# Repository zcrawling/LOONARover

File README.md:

# LOONAR

로버: Raspberry Pi 5 · Control/Payload Teensy 4.1 · RoboClaw.
지상국 명령은 cFS와 vehicle_gatewayd를 거쳐 Control MCU로 전달한다.

## 실행

준비된 Pi에서:

```bash
bash ~/LOONAR/platforms/loonar/tools/start-ground-support.sh --video
```

`--video`는 SSH 접속 PC로 영상을 보낸다. SSH 밖에서는 `--video-ip 지상국IP`를 사용한다.
지상국 PC에서:

```bash
cd ~/LOONAR
bash GCS/scripts/start_loonar_gcs.sh 192.168.0.14
```

주소는 실제 Pi IP로 바꾼다. 웹 화면은 `http://127.0.0.1:8080`이다.

- [Pi 준비·실행·기록](platforms/loonar/porting/ground_control_runbook.md)
- [지상국 사용법](GCS/README.md)
- [Control 펌웨어 빌드·업로드와 배선](platforms/loonar/firmware/control/README.md)
- [Payload 측정](platforms/loonar/porting/payload_pca_runbook.md)
- [구조와 명령 경로](docs/architecture.md) · [문서 목록](docs/README.md)

## 저장소

| 경로 | 내용 |
| --- | --- |
| `GCS/` | 웹 UI, 키보드·Xbox 입력, 영상 수신 |
| `cfs/` | GroundLink, 차량·MCU·Payload 앱 |
| `common/` | Gateway, 통신 codec, 공통 ROS·영상 도구 |
| `platforms/loonar/` | Pi 배포, MCU 펌웨어, 하드웨어·PCB |
| `platforms/limo/` | LIMO 시험 플랫폼과 검증 기록 |
| `tools/` | 통합 시험, 영상·센서·주행 분석 도구 |
| `data/`, `output/` | 실험 원본과 결과 |

문서는 저장소 소스 기준이다. Pi 설치본과 MCU에 업로드된 이미지가 같다는 뜻은 아니다.
날짜가 붙은 측정·제작 기록은 당시 결과로 읽는다.

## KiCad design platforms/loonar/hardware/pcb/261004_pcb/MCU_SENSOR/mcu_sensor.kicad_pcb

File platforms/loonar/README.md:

# LOONAR 로버

Raspberry Pi 5 / Ubuntu 24.04 / ROS 2 Jazzy와 두 Teensy 4.1을 사용한다.
Control은 FreeRTOS·LNR2 USB, Payload는 별도 센서 펌웨어·USB ASCII 경로다.

- [실행·로그·기록](porting/ground_control_runbook.md)
- [Pi 설치](deploy/README.md)
- [배선](hardware/hardware_baseline.md) · [CAD 기반 TF](ros2/loonar_description/README.md)
- [Control 펌웨어](firmware/control/README.md) · [wire v2](porting/mcu_wire_v2.md)
- [Payload 펌웨어](firmware/payload/README.md) · [운용](porting/payload_pca_runbook.md)
- [CubeEye 공급 SDK](vendor-assets.md) · [ToF 기록](porting/tof_recording_runbook.md)

`interfaces/control_mcu_wire_v1.md`와 C 기반 control core는 이전 프로토콜의
회귀시험 자료다. 현재 `src/v2/runtime.cpp`와 혼동하지 않는다.

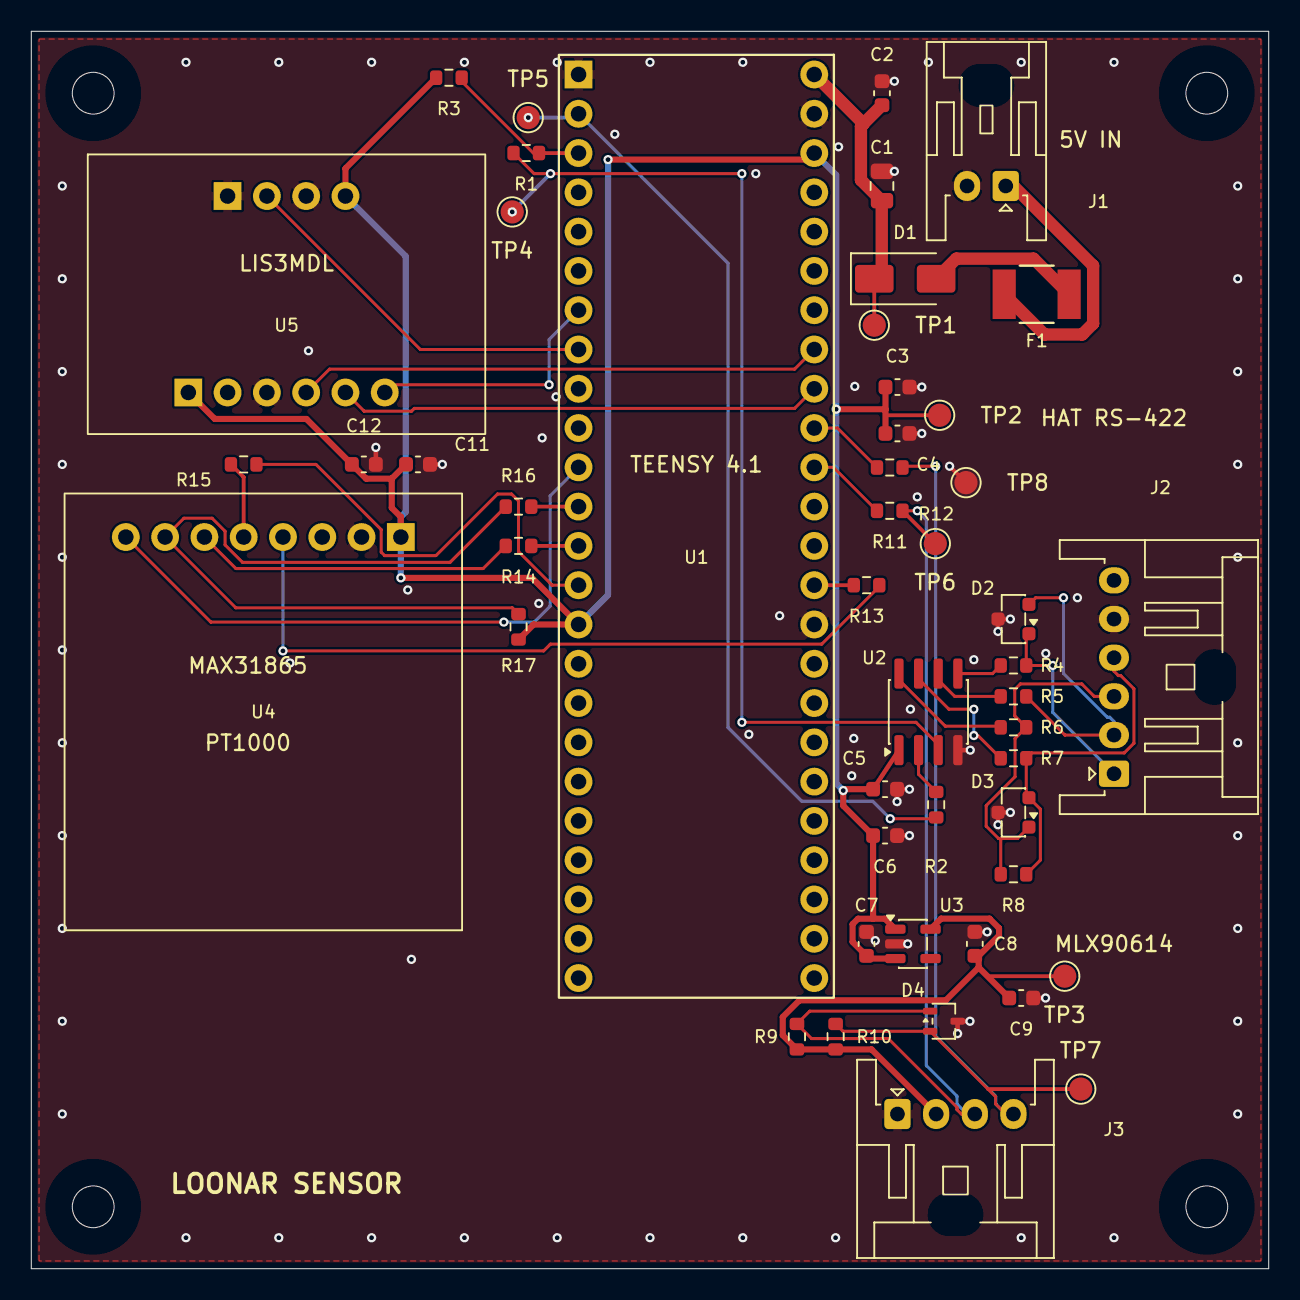
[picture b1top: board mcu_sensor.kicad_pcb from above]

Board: 4 copper layers, 80.0 x 80.0 mm, 53 parts (0 on the bottom side), 35 nets.

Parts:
C1: 10uF / 50V / X5R; C_0805_2012Metric
C2, C4, C5, C9, C11: 100nF / 50V / X7R; C_0603_1608Metric
C3: 4.7uF / 16V / X5R; C_0603_1608Metric
C6, C7, C12: 1uF / 25V / X7R; C_0603_1608Metric
C8: 2.2uF / 10V / X7R; C_0603_1608Metric
D1: B340A-13-F / 40V 3A; D_SMA
D2, D3: CDSOT23-SM712; Bourns_CDSOT23_SM712
D4: TPD2E2U06QDCKRQ1; SOT-323_SC-70
F1: PTC / 0.5A hold / 15V; PTC_Bourns_MF_MSMF050_1812
H1, H2, H3, H4: M2.5 / NPTH 2.7mm; MountingHole_2.7mm_M2.5
J1: 5V IN / XA 2P; JST_XA_S02B-XASK-1_1x02_P2.50mm_Horizontal
J2: HAT RS422 / XA 6P; JST_XA_S06B-XASK-1_1x06_P2.50mm_Horizontal
J3: MLX90614 / XA 4P; JST_XA_S04B-XASK-1_1x04_P2.50mm_Horizontal
R1, R2, R11, R12: 47R; R_0603_1608Metric
R3, R17: 10k; R_0603_1608Metric
R4, R5, R6, R7: 10R / 1% / HP pulse; R_0603_1608Metric
R8: 120R; R_0603_1608Metric
R9, R10: 2.2k; R_0603_1608Metric
R13, R14, R15, R16: 33R / 1%; R_0603_1608Metric
TP1: 5V; TestPoint_Pad_D1.5mm
TP2: 3V3; TestPoint_Pad_D1.5mm
TP3: IR3V; TestPoint_Pad_D1.5mm
TP4: TX; TestPoint_Pad_D1.5mm
TP5: RX; TestPoint_Pad_D1.5mm
TP6: SCL; TestPoint_Pad_D1.5mm
TP7: SDA; TestPoint_Pad_D1.5mm
TP8: GND; TestPoint_Pad_D1.5mm
U1: Teensy 4.1; Teensy41_48Pin
U2: THVD1451DR; SOIC-8_3.9x4.9mm_P1.27mm
U3: TLV75730PDBVR / 3.0V; SOT-23-5
U4: MAX31865 / Rref 4.3k; Adafruit_MAX31865_Carrier
U5: LIS3MDL / Adafruit 4479; Adafruit_LIS3MDL_Carrier

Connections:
+3V0_IR: C8.1, C9.1, J3.2, R9.1, R10.1, TP3.1, U3.5 (OUT)
+3V3: C3.1, C4.1, C5.1, C6.1, C7.1, C11.1, C12.1, R3.1, R17.1, TP2.1, U1.3.3V_1 (3.3V), U1.3.3V_2 (3.3V), U2.1 (VCC), U3.1 (IN), U3.3 (EN), U4.JP1_1 (VIN_3.3V), U5.JP1_4 (CS_-_I2C_HIGH), U5.JP4_1 (VIN_3.3V)
+5V_IN: F1.1, J1.1
+5V_MAIN: C1.1, C2.1, D1.1 (K), TP1.1, U1.VIN (VIN_5V)
FUSED_5V: D1.2 (A), F1.2
GND: C1.2, C2.2, C3.2, C4.2, C5.2, C6.2, C7.2, C8.2, C9.2, C11.2, C12.2, D2.3 (GND), D3.3 (GND), D4.3, J1.2, J2.5, J3.1, TP8.1, U1.GND1 (GND), U1.GND2 (GND), U1.GND3 (GND), U2.4 (GND), U3.2 (GND), U4.JP1_2 (GND), U5.JP1_1 (GND), U5.JP1_3 (DO_/_ADDR), U5.JP4_3 (GND)
IR_SCL: D4.1, J3.3, R9.2, R11.2, TP6.1
IR_SCL_MCU: R11.1, U1.16 (A2)
IR_SDA: D4.2, J3.4, R10.2, R12.2, TP7.1
IR_SDA_MCU: R12.1, U1.17 (A3)
LINK_RX_N: D3.2 (LINE2), J2.4, R7.2, R8.2
LINK_RX_P: D3.1 (LINE1), J2.3, R6.2, R8.1
LINK_TX_N: D2.2 (LINE2), J2.2, R5.2
LINK_TX_P: D2.1 (LINE1), J2.1, R4.2
MAG_DRDY: U1.6 (OUT1D), U5.JP1_2 (DRDY)
MAG_INT: U1.5 (IN2), U5.JP4_6 (INT)
MAG_SCL: U1.19 (A5), U5.JP4_4 (SCL)
MAG_SDA: U1.18 (A4), U5.JP4_5 (SDA)
RS_A: R6.1, U2.8 (A)
RS_B: R7.1, U2.7 (B)
RS_DI: R1.2, TP4.1, U2.3 (D)
RS_RO: R2.1, U2.2 (R)
RS_Y: R4.1, U2.5 (Y)
RS_Z: R5.1, U2.6 (Z)
RTD_CS: R16.2, R17.2, U4.JP1_7 (CS)
RTD_CS_MCU: R16.1, U1.10 (CS1)
RTD_MISO: R15.1, U4.JP1_5 (SDO_/_MISO)
RTD_MOSI: R14.2, U4.JP1_6 (SDI_/_MOSI)
RTD_RDY: U1.9 (OUT1C), U4.JP1_8 (RDY)
RTD_SCK: R13.2, U4.JP1_4 (CLK)
SPI_MISO_MCU: R15.2, U1.12 (MISO)
SPI_MOSI_MCU: R14.1, U1.11 (MOSI)
SPI_SCK_MCU: R13.1, U1.13 (SCK)
UART1_RX: R2.2, TP5.1, U1.0 (RX1)
UART1_TX: R1.1, R3.2, U1.1 (TX1)

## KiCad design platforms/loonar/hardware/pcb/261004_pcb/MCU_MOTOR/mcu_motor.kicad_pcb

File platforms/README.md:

# Vehicle Platforms

Platform folders contain only hardware, firmware, launch/configuration and HIL
assets that genuinely differ between vehicles. Shared mission, ROS autonomy and
Gateway logic belongs in common modules.

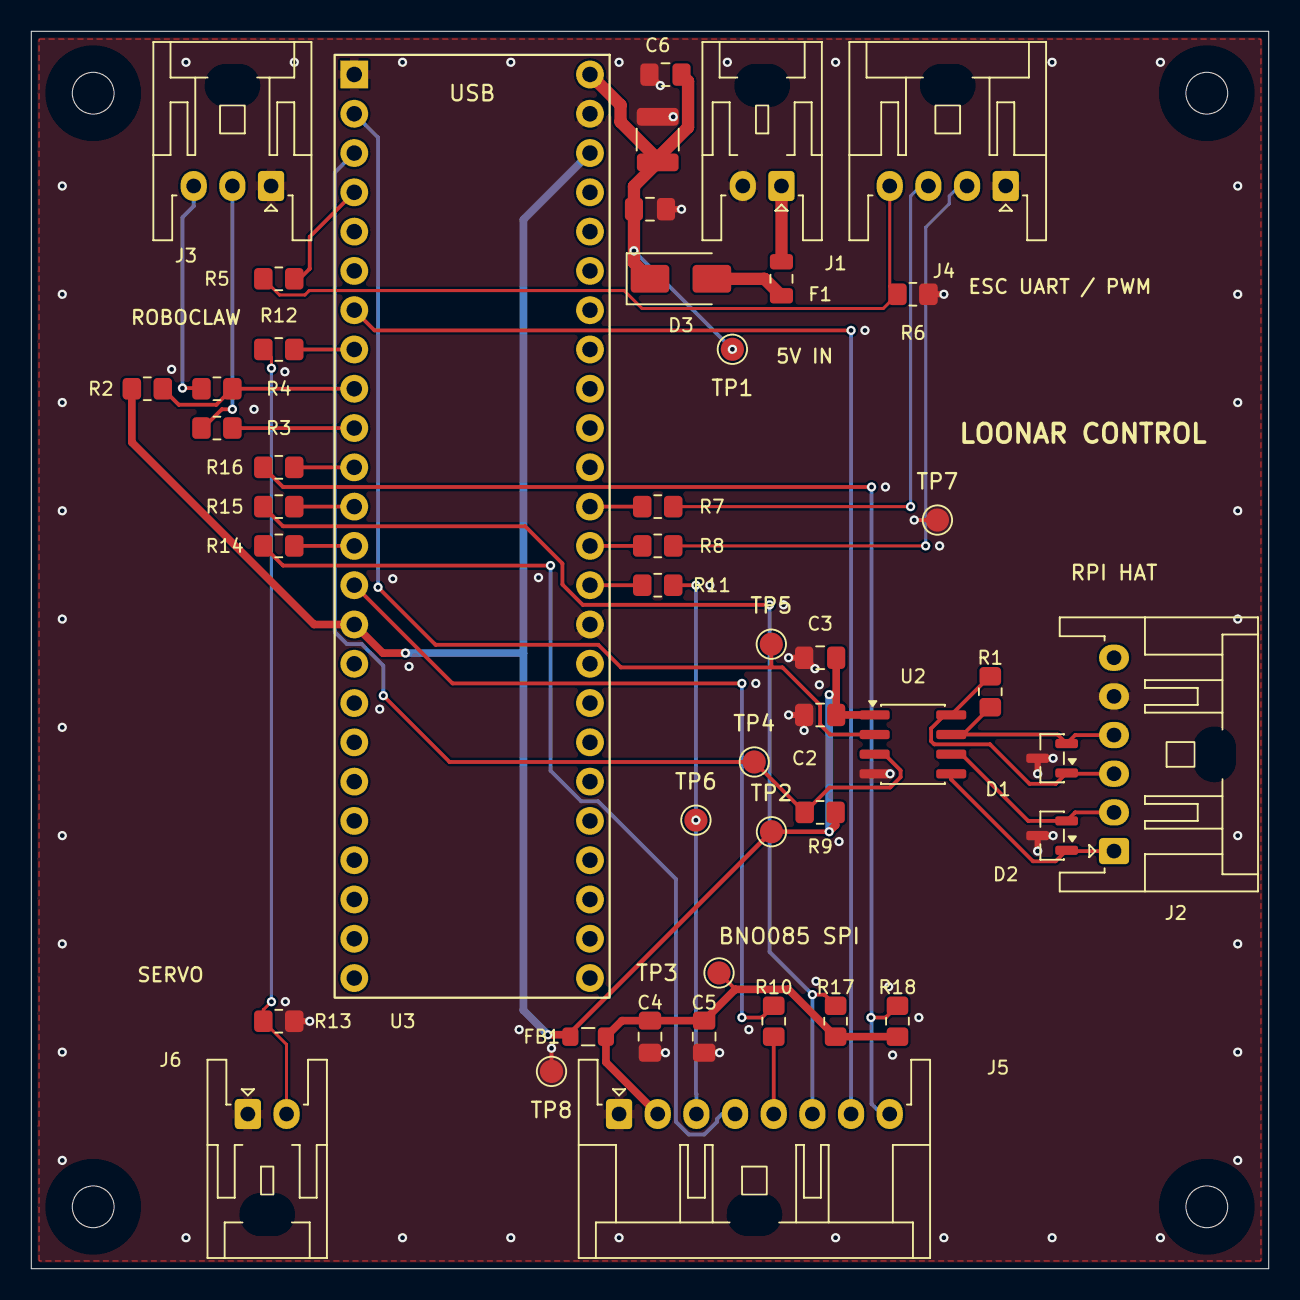
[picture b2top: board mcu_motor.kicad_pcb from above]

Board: 4 copper layers, 80.0 x 80.0 mm, 50 parts (0 on the bottom side), 35 nets.

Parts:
C2, C4, C6: 100nF / 50V / X7R; C_0805_2012Metric_Pad1.18x1.45mm_HandSolder
C3, C8: 1uF / 50V / X7R; C_0805_2012Metric_Pad1.18x1.45mm_HandSolder
C5: 4.7uF / 25V / X5R; C_0805_2012Metric_Pad1.18x1.45mm_HandSolder
C7: 47uF / 16V / X5R; C_1210_3225Metric
D1, D2: SM712-02HTG; SOT-23
D3: B340A-13-F / 40V 3A; D_SMA
F1: PTC / 0.75A hold / 6V; Fuse_MF_PSMF_0805
FB1: 220R@100MHz / 2A; L_0805_2012Metric_Pad1.05x1.20mm_HandSolder
H1, H2, H3, H4: M2.5 / NPTH 2.7mm; MountingHole_2.7mm_M2.5
J1: 5V IN / XA 2P; JST_XA_S02B-XASK-1_1x02_P2.50mm_Horizontal
J2: HAT RS422 / XA 6P; JST_XA_S06B-XASK-1_1x06_P2.50mm_Horizontal
J3: RoboClaw UART / XA 3P; JST_XA_S03B-XASK-1_1x03_P2.50mm_Horizontal
J4: ESC UART PWM / XA 4P; JST_XA_S04B-XASK-1_1x04_P2.50mm_Horizontal
J5: BNO085 SPI / XA 8P; JST_XA_S08B-XASK-1_1x08_P2.50mm_Horizontal
J6: TR5 PWM / XA 2P; JST_XA_S02B-XASK-1_1x02_P2.50mm_Horizontal
R1: 120R / 1%; R_0805_2012Metric_Pad1.20x1.40mm_HandSolder
R2: 4.7k / 1%; R_0805_2012Metric_Pad1.20x1.40mm_HandSolder
R3, R4, R5, R7, R8, R12, R16: 100R / 1%; R_0805_2012Metric_Pad1.20x1.40mm_HandSolder
R6, R9, R13, R17, R18: 10k / 1%; R_0805_2012Metric_Pad1.20x1.40mm_HandSolder
R10, R11, R14, R15: 33R / 1%; R_0805_2012Metric_Pad1.20x1.40mm_HandSolder
TP1: 5V; TestPoint_Pad_D1.5mm
TP2: 3V3; TestPoint_Pad_D1.5mm
TP3: IMU3V; TestPoint_Pad_D1.5mm
TP4: TX; TestPoint_Pad_D1.5mm
TP5: RX; TestPoint_Pad_D1.5mm
TP6: SCK; TestPoint_Pad_D1.5mm
TP7, TP8: GND; TestPoint_Pad_D1.5mm
U2: THVD1451DR; SOIC-8_3.9x4.9mm_P1.27mm
U3: Teensy 4.1; Teensy41_48Pin

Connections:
5V_IN: F1.1, J1.1
+3V3: C2.1, C3.1, FB1.1, R2.1, R9.2, TP2.1, U2.1 (VCC), U3.3.3V_1 (3.3V), U3.3.3V_2 (3.3V)
+3V3_IMU: C4.2, C5.2, FB1.2, J5.2, R17.1, R18.1, TP3.1
+5V_MAIN: C6.1, C7.1, C8.1, D3.1 (K), TP1.1, U3.VIN (VIN_5V)
B-G431B RX: J4.2, R8.1
B-G431B TX: J4.3, R7.1
B_G431B PWM: J4.4, R5.1, R6.1
GND: C2.2, C3.2, C4.1, C5.1, C6.2, C7.2, C8.2, D1.3 (common), D2.3 (common), J1.2, J2.5, J3.1, J4.1, J5.1, J6.1, R6.2, R13.2, TP7.1, TP8.1, U2.4 (GND), U3.GND1 (GND), U3.GND2 (GND), U3.GND3 (GND)
IMU_CS: J5.6, R15.1, R17.2
IMU_CS_MCU: R15.2, U3.10 (CS1)
IMU_INT: J5.7, U3.5 (IN2)
IMU_MISO: J5.5, R10.1
IMU_MISO_MCU: R10.2, U3.12 (MISO)
IMU_MOSI: J5.4, R14.1
IMU_MOSI_MCU: R14.2, U3.11 (MOSI)
IMU_RST: J5.8, R16.1, R18.2
IMU_RST_MCU: R16.2, U3.9 (OUT1C)
IMU_SCK: J5.3, R11.1, TP6.1
IMU_SCK_MCU: R11.2, U3.13 (SCK)
unnamed: D3.2 (A), F1.2
RS485_RX+: D1.1 (A1), J2.3, R1.1, U2.8 (A)
RS485_RX-: D1.2 (A2), J2.4, R1.2, U2.7 (B)
RS485_TX+: D2.1 (A1), J2.1, U2.5 (Y)
RS485_TX-: D2.2 (A2), J2.2, U2.6 (Z)
RoboClaw RX: J3.2, R3.1
RoboClaw TX: J3.3, R4.1
SERVO_PWM: J6.2, R12.1, R13.1
SERVO_PWM_MCU: R12.2, U3.6 (OUT1D)
Teensy_Pin2: R5.2, U3.2 (OUT2)
Teensy_RX1: TP5.1, U2.2 (R), U3.0 (RX1)
Teensy_RX2: R2.2, R4.2, U3.7 (RX2)
Teensy_RX3: R7.2, U3.15 (A1)
Teensy_TX1: R9.1, TP4.1, U2.3 (D), U3.1 (TX1)
Teensy_TX2: R3.2, U3.8 (TX2)
Teensy_TX3: R8.2, U3.14 (A0)

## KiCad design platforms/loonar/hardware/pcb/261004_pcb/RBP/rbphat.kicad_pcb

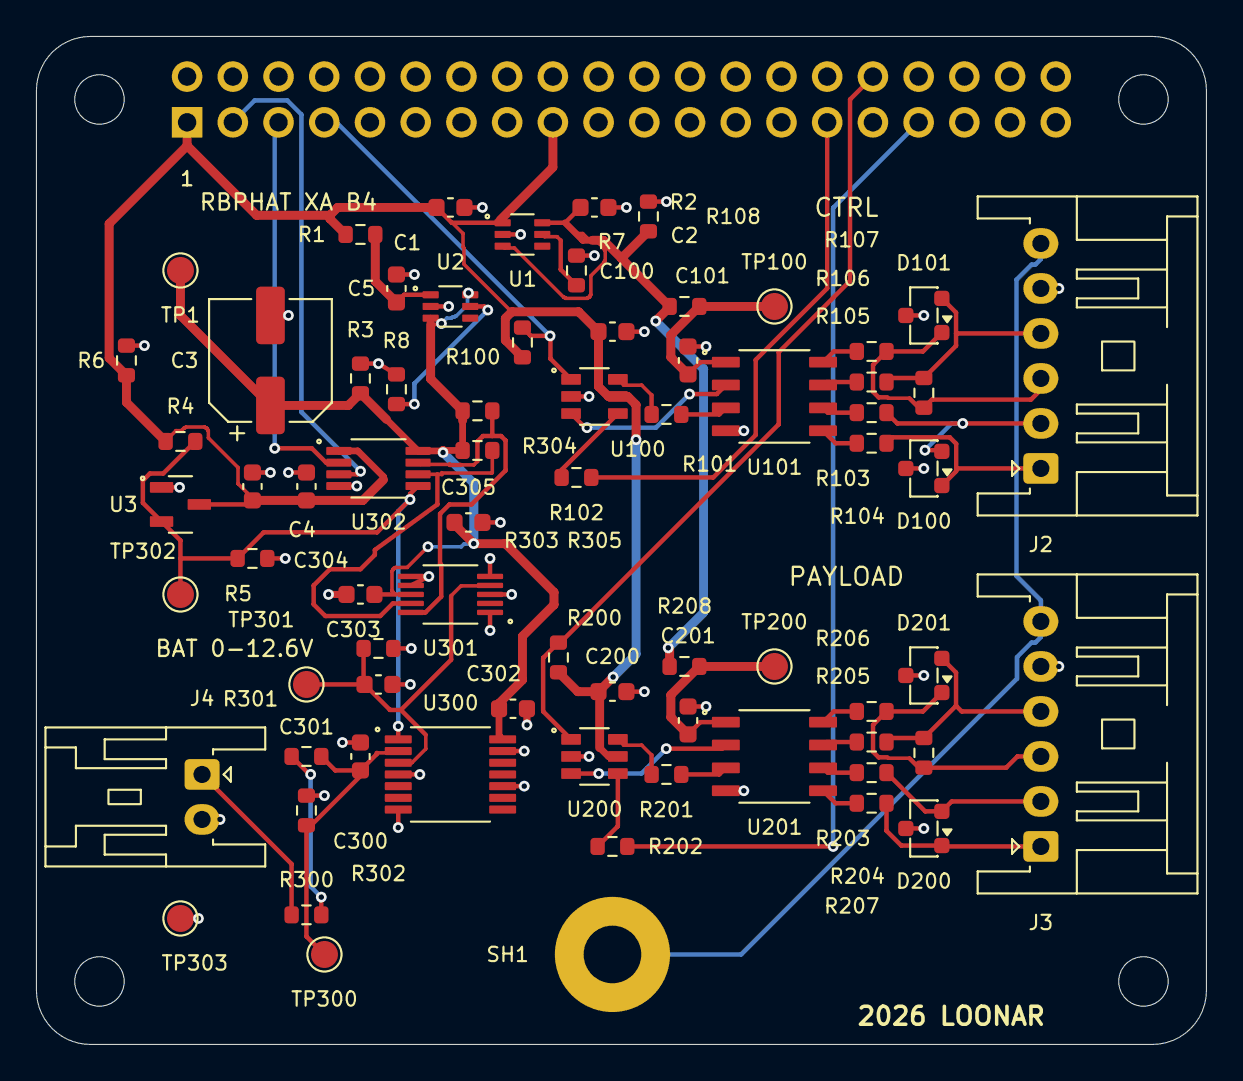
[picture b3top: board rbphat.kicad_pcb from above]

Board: 4 copper layers, 65.0 x 56.0 mm, 77 parts (1 on the bottom side), 47 nets.

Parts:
C1, C5, C300: 1uF / 25V / X7R; Capacitor_SMD_C_0603_1608Metric
C2: 4.7uF / 16V / X5R; Capacitor_SMD_C_0603_1608Metric
C3: 100uF / 16V / polarized; Panasonic_FK_D_6.3x5.8
C4, C100, C101, C200, C201, C302, C303, C304, C305: 100nF / 50V / X7R; Capacitor_SMD_C_0603_1608Metric
C301: 1nF / 50V / C0G; Capacitor_SMD_C_0603_1608Metric
D100, D101, D200, D201: CDSOT23-SM712; Bourns_CDSOT23_SM712
H1, H2, H3, H4: M2.5 / NPTH 2.75mm
J1: Raspberry Pi GPIO / 2x20; GPIO_2x20_H16_Drill1.02
J2: CTRL RS422 / XA 6P; XA_S06B_Horizontal
J3: PAYLOAD RS422 / XA 6P; XA_S06B_Horizontal
J4: BAT 0-12.6V / XA 2P; XA_S02B_Horizontal
R1: 22R / 1% / HP pulse; Resistor_SMD_R_0603_1608Metric
R2, R3, R4, R7, R8, R100, R200: 10k; Resistor_SMD_R_0603_1608Metric
R5: 100k; Resistor_SMD_R_0603_1608Metric
R6: 1k; Resistor_SMD_R_0603_1608Metric
R101, R102, R201, R202: 47R; Resistor_SMD_R_0603_1608Metric
R103, R104, R105, R106, R203, R204, R205, R206: 10R / 1% / HP pulse; Resistor_SMD_R_0603_1608Metric
R107, R207: 120R; Resistor_SMD_R_0603_1608Metric
R108, R208: 0R; Resistor_SMD_R_0603_1608Metric
R300, R301, R303: 47k / 0.1%; Resistor_SMD_R_0603_1608Metric
R302: 18k / 0.1%; Resistor_SMD_R_0603_1608Metric
R304, R305: 4.7k; Resistor_SMD_R_0603_1608Metric
SH1: CHASSIS / M3 ring terminal; Chassis_M3_Plated
TP1: ANA supply; TestPoint_TestPoint_Pad_D1.5mm
TP100: CTRL_VCC; TestPoint_TestPoint_Pad_D1.5mm
TP200: PAY_VCC; TestPoint_TestPoint_Pad_D1.5mm
TP300: BAT_DIV; TestPoint_TestPoint_Pad_D1.5mm
TP301: BAT_ADC; TestPoint_TestPoint_Pad_D1.5mm
TP302: POWER_GOOD; TestPoint_TestPoint_Pad_D1.5mm
TP303: GND; TestPoint_TestPoint_Pad_D1.5mm
U1, U2: LM66100DCKR; TI_DCK0006A
U3: TLV803ED29DBZR; TI_DBZ0003A
U100, U200: SN74LVC2G17DBVT; TI_DBV0006A
U101, U201: THVD1451DR; TI_D0008A
U300: TMUX1511PWR; TI_PW0014A
U301: ADS1115IDGSR; TI_DGS0010A
U302: TCA9517ADGKR; TI_DGK0008A

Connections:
+3V3_ANA: C3.1, C302.1, C303.1, C305.1, R3.1, R304.1, R305.1, TP1.1, U2.3, U2.6, U300.14, U301.8, U302.8
+3V3_PI: C1.1, C4.1, C100.1, C200.1, C304.1, J1.1, J1.17, R1.1, R4.1, R6.1, R100.1, R200.1, U1.1, U3.3, U100.5, U200.5, U302.1
+3V3_RS: C2.1, R2.1, R108.1, R208.1, U1.3, U1.6
/ANA_FEED: C5.1, R1.2, U2.1
/ANA_STATUS_UNUSED: R8.1, U2.5
/Battery sensing and I2C isolation/ADC_SCL: R304.2, U301.10, U302.7
/Battery sensing and I2C isolation/ADC_SDA: R305.2, U301.9, U302.6
/Battery sensing and I2C isolation/BAT_ADC: C301.1, R303.1, TP301.1, U300.3, U301.4
/Battery sensing and I2C isolation/BAT_DIV: C300.1, R301.2, R302.1, TP300.1, U300.2
/Battery sensing and I2C isolation/BAT_MID: R300.2, R301.1
/Battery sensing and I2C isolation/BAT_RAW: J4.1, R300.1
/CTRL full-duplex RS-422/CTRL_A: R105.1, U101.8
/CTRL full-duplex RS-422/CTRL_B: R106.1, U101.7
/CTRL full-duplex RS-422/CTRL_DI: R101.2, U101.3
/CTRL full-duplex RS-422/CTRL_RO: U100.3, U101.2
/CTRL full-duplex RS-422/CTRL_RX+: D101.1, J2.3, R105.2, R107.1
/CTRL full-duplex RS-422/CTRL_RX-: D101.2, J2.4, R106.2, R107.2
/CTRL full-duplex RS-422/CTRL_RX_BUF: R102.1, U100.4
/CTRL full-duplex RS-422/CTRL_TX+: D100.1, J2.1, R103.2
/CTRL full-duplex RS-422/CTRL_TX-: D100.2, J2.2, R104.2
/CTRL full-duplex RS-422/CTRL_TX_BUF: R101.1, U100.6
/CTRL full-duplex RS-422/CTRL_VCC: C101.1, R108.2, TP100.1, U101.1
/CTRL full-duplex RS-422/CTRL_Y: R103.1, U101.5
/CTRL full-duplex RS-422/CTRL_Z: R104.1, U101.6
/PAY full-duplex RS-422/PAY_A: R205.1, U201.8
/PAY full-duplex RS-422/PAY_B: R206.1, U201.7
/PAY full-duplex RS-422/PAY_DI: R201.2, U201.3
/PAY full-duplex RS-422/PAY_RO: U200.3, U201.2
/PAY full-duplex RS-422/PAY_RX+: D201.1, J3.3, R205.2, R207.1
/PAY full-duplex RS-422/PAY_RX-: D201.2, J3.4, R206.2, R207.2
/PAY full-duplex RS-422/PAY_RX_BUF: R202.1, U200.4
/PAY full-duplex RS-422/PAY_TX+: D200.1, J3.1, R203.2
/PAY full-duplex RS-422/PAY_TX-: D200.2, J3.2, R204.2
/PAY full-duplex RS-422/PAY_TX_BUF: R201.1, U200.6
/PAY full-duplex RS-422/PAY_VCC: C201.1, R208.2, TP200.1, U201.1
/PAY full-duplex RS-422/PAY_Y: R203.1, U201.5
/PAY full-duplex RS-422/PAY_Z: R204.1, U201.6
/RS_STATUS_UNUSED: R7.1, U1.5
CHASSIS: J2.6, J3.6, SH1.1
CTRL_RX: J1.29, R102.2
CTRL_TX: J1.7, R100.2, U100.1
GND: C1.2, C2.2, C3.2, C4.2, C5.2, C100.2, C101.2, C200.2, C201.2, C300.2, C301.2, C302.2, C303.2, C304.2, C305.2, D100.3, D101.3, D200.3, D201.3, J1.6, J1.9, J1.14, J1.20, J1.25, J1.30, J1.34, J1.39, J2.5, J3.5, J4.2, R2.2, R3.2, R5.2, R6.2, R7.2, R8.2, R302.2, R303.2, TP303.1, U1.2, U2.2, U3.1, U100.2, U101.4, U200.2, U201.4, U300.4, U300.7, U300.10, U300.13, U301.1, U301.3, U301.5, U301.6, U301.7, U302.4
PAY_RX: J1.33, R202.2
PAY_TX: J1.32, R200.2, U200.1
PI_SCL: J1.5, U302.2
PI_SDA: J1.3, U302.3
POWER_GOOD: R4.2, R5.1, TP302.1, U3.2, U300.1, U302.5

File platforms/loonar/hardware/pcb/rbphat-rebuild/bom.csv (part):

reference,value,mpn,footprint,dnp,sheet,datasheet
J1,Pi 5 / H16 / gap19,PRT-16763,RBPHAT:GPIO_2x20_H16_Drill1.02,False,rbphat,https://cdn.sparkfun.com/assets/0/b/8/5/2/DS-16763-2_X_20_Pi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
U1,LM66100DCKR,LM66100DCKR,RBPHAT:TI_DCK0006A,False,rbphat,https://www.ti.com/lit/ds/symlink/lm66100.pdf
U2,LM66100DCKR,LM66100DCKR,RBPHAT:TI_DCK0006A,False,rbphat,https://www.ti.com/lit/ds/symlink/lm66100.pdf
R7,10k,CRCW060310K0FKEA,RBPHAT:Resistor_SMD_R_0603_1608Metric,False,rbphat,https://www.vishay.com/docs/20035/dcrcwe3.pdf
R8,10k,CRCW060310K0FKEA,RBPHAT:Resistor_SMD_R_0603_1608Metric,False,rbphat,https://www.vishay.com/docs/20035/dcrcwe3.pdf
R1,22R pulse,CRCW060322R0FKEAHP,RBPHAT:Resistor_SMD_R_0603_1608Metric,False,rbphat,https://www.vishay.com/docs/20043/crcwhpe3.pdf
C1,1u / 25V / X7R,GRM188R71E105KA12D,RBPHAT:Capacitor_SMD_C_0603_1608Metric,False,rbphat,https://www.murata.com/products/productdetail?partno=GRM188R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
C2,4.7u / 10V / X5R,GRM188R61A475KE15D,RBPHAT:Capacitor_SMD_C_0603_1608Metric,False,rbphat,https://www.murata.com/products/productdetail?partno=GRM188R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
C3,100u / 16V / 20%,EEEFK1C101P,RBPHAT:Panasonic_FK_D_6.3x5.8,False,rbphat,https://api.pim.na.industrial.panasonic.com/file_stream/main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
R2,10k,CRCW060310K0FKEA,RBPHAT:Resistor_SMD_R_0603_1608Metric,False,rbphat,https://www.vishay.com/docs/20035/dcrcwe3.pdf
R3,10k,CRCW060310K0FKEA,RBPHAT:Resistor_SMD_R_0603_1608Metric,False,rbphat,https://www.vishay.com/docs/20035/dcrcwe3.pdf
U3,TLV803ED29DBZR,TLV803ED29DBZR,RBPHAT:TI_DBZ0003A,False,rbphat,https://www.ti.com/lit/ds/symlink/tlv803e.pdf
R4,10k,CRCW060310K0FKEA,RBPHAT:Resistor_SMD_R_0603_1608Metric,False,rbphat,https://www.vishay.com/docs/20035/dcrcwe3.pdf
R5,100k,CRCW0603100KFKEA,RBPHAT:Resistor_SMD_R_0603_1608Metric,False,rbphat,https://www.vishay.com/docs/20035/dcrcwe3.pdf
R6,1k,CRCW06031K00FKEA,RBPHAT:Resistor_SMD_R_0603_1608Metric,False,rbphat,https://www.vishay.com/docs/20035/dcrcwe3.pdf
C4,100n / 16V / X7R,GRM188R71C104KA01D,RBPHAT:Capacitor_SMD_C_0603_1608Metric,False,rbphat,https://www.murata.com/products/productdetail?partno=GRM188R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
C5,1u / 25V / X7R,GRM188R71E105KA12D,RBPHAT:Capacitor_SMD_C_0603_1608Metric,False,rbphat,https://www.murata.com/products/productdetail?partno=GRM188R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
TP1,ANA supply,PCB feature - no purchased part,RBPHAT:TestPoint_TestPoint_Pad_D1.5mm,False,rbphat,
U100,SN74LVC2G17DBVR,SN74LVC2G17DBVR,RBPHAT:TI_DBV0006A,False,control,https://www.ti.com/lit/ds/symlink/sn74lvc2g17.pdf
U101,THVD1451DR,THVD1451DR,RBPHAT:TI_D0008A,False,control,https://www.ti.com/lit/ds/symlink/thvd1451.pdf
J2,BM05B-GHS-TBT,BM05B-GHS-TBT(LF)(SN),RBPHAT:Connector_JST_JST_GH_BM05B-GHS-TBT_1x05-1MP_P1.25mm_Vertical,False,control,https://www.jst-mfg.com/product/pdf/eng/eGH.pdf
R108,0R / rail link,CRCW06030000Z0EA,RBPHAT:Resistor_SMD_R_0603_1608Metric,False,control,https://www.vishay.com/docs/20035/dcrcwe3.pdf
TP100,CTRL_VCC,PCB feature - no purchased part,RBPHAT:TestPoint_TestPoint_Pad_D1.5mm,False,control,
R100,10k,CRCW060310K0FKEA,RBPHAT:Resistor_SMD_R_0603_1608Metric,False,control,https://www.vishay.com/docs/20035/dcrcwe3.pdf
R101,47R,CRCW060347R0FKEA,RBPHAT:Resistor_SMD_R_0603_1608Metric,False,control,https://www.vishay.com/docs/20035/dcrcwe3.pdf
R102,47R,CRCW060347R0FKEA,RBPHAT:Resistor_SMD_R_0603_1608Metric,False,control,https://www.vishay.com/docs/20035/dcrcwe3.pdf
R103,10R pulse,CRCW0603010RJNEAHP,RBPHAT:Resistor_SMD_R_0603_1608Metric,False,control,https://www.vishay.com/docs/20043/crcwhpe3.pdf
R104,10R pulse,CRCW0603010RJNEAHP,RBPHAT:Resistor_SMD_R_0603_1608Metric,False,control,https://www.vishay.com/docs/20043/crcwhpe3.pdf
R105,10R pulse,CRCW0603010RJNEAHP,RBPHAT:Resistor_SMD_R_0603_1608Metric,False,control,https://www.vishay.com/docs/20043/crcwhpe3.pdf
R106,10R pulse,CRCW0603010RJNEAHP,RBPHAT:Resistor_SMD_R_0603_1608Metric,False,control,https://www.vishay.com/docs/20043/crcwhpe3.pdf
R107,120R / DNP,CRCW0603120RFKEA,RBPHAT:Resistor_SMD_R_0603_1608Metric,True,control,https://www.vishay.com/docs/20035/dcrcwe3.pdf
D100,CDSOT23-SM712,CDSOT23-SM712,RBPHAT:Bourns_CDSOT23_SM712,False,control,https://www.bourns.com/pdfs/CDSOT23-SM712.pdf
D101,CDSOT23-SM712,CDSOT23-SM712,RBPHAT:Bourns_CDSOT23_SM712,False,control,https://www.bourns.com/pdfs/CDSOT23-SM712.pdf
C100,100n / 16V / X7R,GRM188R71C104KA01D,RBPHAT:Capacitor_SMD_C_0603_1608Metric,False,control,https://www.murata.com/products/productdetail?partno=GRM188R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
C101,100n / 16V / X7R,GRM188R71C104KA01D,RBPHAT:Capacitor_SMD_C_0603_1608Metric,False,control,https://www.murata.com/products/productdetail?partno=GRM188R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
U200,SN74LVC2G17DBVR,SN74LVC2G17DBVR,RBPHAT:TI_DBV0006A,False,payload,https://www.ti.com/lit/ds/symlink/sn74lvc2g17.pdf
U201,THVD1451DR,THVD1451DR,RBPHAT:TI_D0008A,False,payload,https://www.ti.com/lit/ds/symlink/thvd1451.pdf
J3,BM05B-GHS-TBT,BM05B-GHS-TBT(LF)(SN),RBPHAT:Connector_JST_JST_GH_BM05B-GHS-TBT_1x05-1MP_P1.25mm_Vertical,False,payload,https://www.jst-mfg.com/product/pdf/eng/eGH.pdf
R208,0R / rail link,CRCW06030000Z0EA,RBPHAT:Resistor_SMD_R_0603_1608Metric,False,payload,https://www.vishay.com/docs/20035/dcrcwe3.pdf
TP200,PAY_VCC,PCB feature - no purchased part,RBPHAT:TestPoint_TestPoint_Pad_D1.5mm,False,payload,
R200,10k,CRCW060310K0FKEA,RBPHAT:Resistor_SMD_R_0603_1608Metric,False,payload,https://www.vishay.com/docs/20035/dcrcwe3.pdf
R201,47R,CRCW060347R0FKEA,RBPHAT:Resistor_SMD_R_0603_1608Metric,False,payload,https://www.vishay.com/docs/20035/dcrcwe3.pdf
R202,47R,CRCW060347R0FKEA,RBPHAT:Resistor_SMD_R_0603_1608Metric,False,payload,https://www.vishay.com/docs/20035/dcrcwe3.pdf
R203,10R pulse,CRCW0603010RJNEAHP,RBPHAT:Resistor_SMD_R_0603_1608Metric,False,payload,https://www.vishay.com/docs/20043/crcwhpe3.pdf
R204,10R pulse,CRCW0603010RJNEAHP,RBPHAT:Resistor_SMD_R_0603_1608Metric,False,payload,https://www.vishay.com/docs/20043/crcwhpe3.pdf
R205,10R pulse,CRCW0603010RJNEAHP,RBPHAT:Resistor_SMD_R_0603_1608Metric,False,payload,https://www.vishay.com/docs/20043/crcwhpe3.pdf
R206,10R pulse,CRCW0603010RJNEAHP,RBPHAT:Resistor_SMD_R_0603_1608Metric,False,payload,https://www.vishay.com/docs/20043/crcwhpe3.pdf
R207,120R / DNP,CRCW0603120RFKEA,RBPHAT:Resistor_SMD_R_0603_1608Metric,True,payload,https://www.vishay.com/docs/20035/dcrcwe3.pdf
D200,CDSOT23-SM712,CDSOT23-SM712,RBPHAT:Bourns_CDSOT23_SM712,False,payload,https://www.bourns.com/pdfs/CDSOT23-SM712.pdf
D201,CDSOT23-SM712,CDSOT23-SM712,RBPHAT:Bourns_CDSOT23_SM712,False,payload,https://www.bourns.com/pdfs/CDSOT23-SM712.pdf
C200,100n / 16V / X7R,GRM188R71C104KA01D,RBPHAT:Capacitor_SMD_C_0603_1608Metric,False,payload,https://www.murata.com/products/productdetail?partno=GRM188R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
C201,100n / 16V / X7R,GRM188R71C104KA01D,RBPHAT:Capacitor_SMD_C_0603_1608Metric,False,payload,https://www.murata.com/products/productdetail?partno=GRM188R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
J4,Battery sense only,BM02B-GHS-TBT(LF)(SN),RBPHAT:Connector_JST_JST_GH_BM02B-GHS-TBT_1x02-1MP_P1.25mm_Vertical,False,battery,https://www.jst-mfg.com/product/pdf/eng/eGH.pdf
R300,47k / 0.1%,TNPW060347K0BEEA,RBPHAT:Resistor_SMD_R_0603_1608Metric,False,battery,https://www.vishay.com/docs/28758/tnpw_e3.pdf
R301,47k / 0.1%,TNPW060347K0BEEA,RBPHAT:Resistor_SMD_R_0603_1608Metric,False,battery,https://www.vishay.com/docs/28758/tnpw_e3.pdf
R302,18k / 0.1%,TNPW060318K0BEEA,RBPHAT:Resistor_SMD_R_0603_1608Metric,False,battery,https://www.vishay.com/docs/28758/tnpw_e3.pdf
C300,1u / 25V / X7R,GRM188R71E105KA12D,RBPHAT:Capacitor_SMD_C_0603_1608Metric,False,battery,https://www.murata.com/products/productdetail?partno=GRM188R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
U300,TMUX1511PWR,TMUX1511PWR,RBPHAT:TI_PW0014A,False,battery,https://www.ti.com/lit/ds/symlink/tmux1511.pdf
U301,ADS1115IDGSR,ADS1115IDGSR,RBPHAT:TI_DGS0010A,False,battery,https://www.ti.com/lit/ds/symlink/ads1115.pdf
R303,47k / 0.1%,TNPW060347K0BEEA,RBPHAT:Resistor_SMD_R_0603_1608Metric,False,battery,https://www.vishay.com/docs/28758/tnpw_e3.pdf
C301,1n / 50V / C0G,GRM1885C1H102JA01D,RBPHAT:Capacitor_SMD_C_0603_1608Metric,False,battery,https://www.murata.com/products/productdetail?partno=GRM1885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
